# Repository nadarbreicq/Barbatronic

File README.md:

# Barbatronic

Ce git répertorie la plupart des projets présentés lors des Lives Twitch et des vidéos Youtubes de la chaine Barbatronic. Pour les projets liés à la Coupe de France de robotique, vosu pouvez retrouver les sources dans les repo de l'équipe des Karibous (https://github.com/LesKaribous)

Les projets sont triés par type plutôt que par numéro de live ou de vidéos car un projet peut être présenté plusieurs fois sur plusieurs supports différents.

Tous les projets de la chaine ne sont pas (encore) sur ce repo. Je suis en train de rapatrier les projets depuis Fusion360 et Egale, mais cela peut prendre un peu de temps. Si il vous manque un projet, n'hésitez pas à me contacter.

## Logiciels utilisés :

FreeCAD 0.19 de Real thunder : https://github.com/realthunder/FreeCAD_assembly3/releases/tag/0.11

Inkscape 1.0.1 : https://inkscape.org/release/inkscape-1.0.1/

K40 Whisperer : https://www.scorchworks.com/K40whisperer/k40whisperer.html

Eagle : https://www.autodesk.fr/products/eagle

Cura : https://ultimaker.com/fr/software/ultimaker-cura

## Socials :

Youtube   : https://www.youtube.com/barbatroniclive

Twitch    : https://www.twitch.tv/barbatroniclive

Twitter   : https://twitter.com/barbatronic

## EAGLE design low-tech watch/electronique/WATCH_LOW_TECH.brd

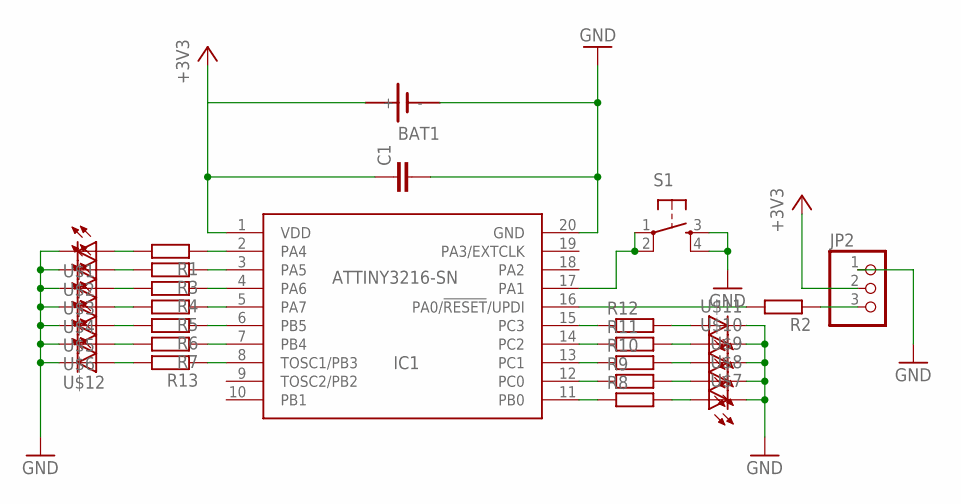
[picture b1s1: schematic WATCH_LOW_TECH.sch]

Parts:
BAT1: SN2032
C1: C-EUC1206; C1206
IC1: ATTINY3216-SN; SOIC127P1030X265-20N
JP2: PINHD-1X03_2.54; 1X03
R1, R2, R3, R4, R5, R6, R7, R8, R9, R10, R11, R12, R13: R-EU_R1206; R1206
S1: 6MM_SWITCH6MM_SWITCH; 6MM_SWITCH
U$1, U$2, U$3, U$4, U$5, U$6, U$7, U$8, U$9, U$10, U$11, U$12: LEDFAB1206; LED1206FAB

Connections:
+3V3: BAT1.+, C1.1, IC1.1 (VDD), JP2.2
GND: BAT1.-, C1.2, IC1.20 (GND), JP2.1, S1.3 (S), S1.4 (S1), U$1.2 (C), U$2.2 (C), U$3.2 (C), U$4.2 (C), U$5.2 (C), U$6.2 (C), U$7.2 (C), U$8.2 (C), U$9.2 (C), U$10.2 (C), U$11.2 (C), U$12.2 (C)
unnamed: R1.2, U$1.1 (A)
unnamed: IC1.2 (PA4), R1.1
unnamed: IC1.16 (PA0/!RESET!/UPDI), R2.2
unnamed: JP2.3, R2.1
unnamed: IC1.11 (PB0), R8.1
unnamed: IC1.12 (PC0), R9.1
unnamed: IC1.13 (PC1), R10.1
unnamed: IC1.14 (PC2), R11.1
unnamed: IC1.15 (PC3), R12.1
unnamed: IC1.8 (TOSC1/PB3), R13.1
unnamed: IC1.7 (PB4), R7.1
unnamed: IC1.6 (PB5), R6.1
unnamed: IC1.5 (PA7), R5.1
unnamed: IC1.4 (PA6), R4.1
unnamed: IC1.3 (PA5), R3.1
unnamed: R3.2, U$2.1 (A)
unnamed: R4.2, U$3.1 (A)
unnamed: R5.2, U$4.1 (A)
unnamed: R6.2, U$5.1 (A)
unnamed: R7.2, U$6.1 (A)
unnamed: R13.2, U$12.1 (A)
unnamed: R12.2, U$11.1 (A)
unnamed: R11.2, U$10.1 (A)
unnamed: R10.2, U$9.1 (A)
unnamed: R9.2, U$8.1 (A)
unnamed: R8.2, U$7.1 (A)
unnamed: IC1.17 (PA1), S1.1, S1.2 (P1)

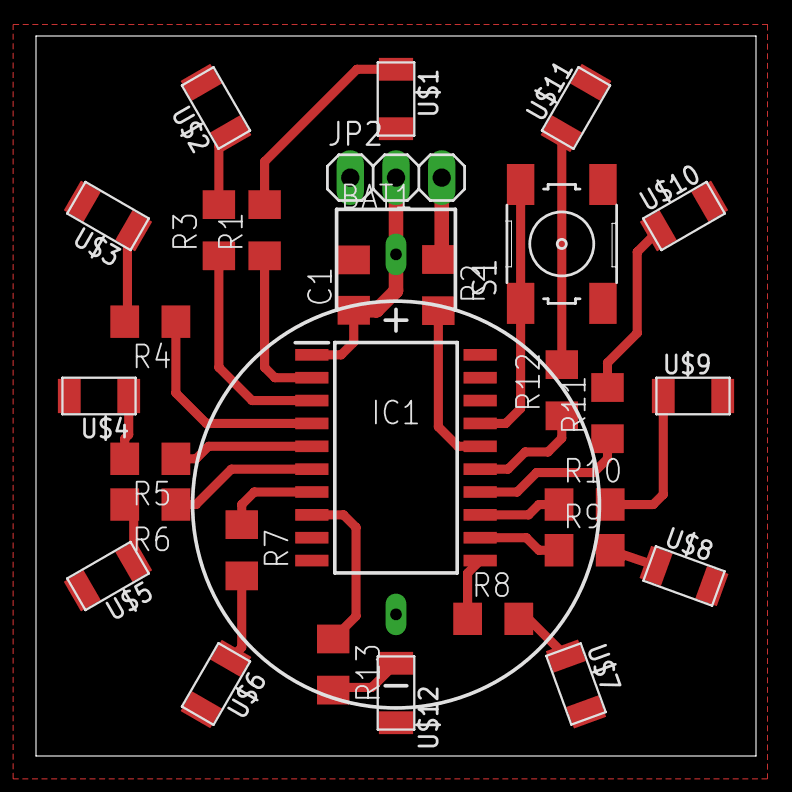
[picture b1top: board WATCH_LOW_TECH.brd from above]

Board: 2 copper layers, 40.0 x 40.0 mm, 30 parts (0 on the bottom side), 29 nets.

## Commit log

2020-11-18 typo
2020-11-19 first upload
2020-11-23 live 65
2020-11-23 Update list
2020-11-23 update prices
2020-11-23 fix table
2020-12-01 add k40.se site
2020-12-01 add infos
2020-12-07 live 67
2020-12-13 live 68
2020-12-17 new StickVise hack
2020-12-17 change directories
2020-12-23 creation
2020-12-23 update description and image
2021-01-10 multi upload
2021-01-11 live 71
2021-01-14 add ref
2021-01-31 Set theme jekyll-theme-minimal
2021-01-31 Create CNAME
2021-01-31 Update CNAME
2021-02-08 huge upload
2021-02-08 Add KiCAD files autosave
2021-03-02 hovercraft project
2021-03-02 Add support bobine
2021-03-02 Change repo
2021-03-02 BoxGenerator first commit
2021-03-06 bad constraint
2021-03-06 Cadres des vues
    Affichage du cadre des vues activé par défaut dans le fichier.
2021-11-28 projet #2
